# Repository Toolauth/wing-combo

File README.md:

# Combined Use Board
This is the **flagship board** for the [Toolauth](https://github.com/Toolauth) project.  More information about use, setup, and firmware is available in [this repo's wiki](https://github.com/Toolauth/wing-combo/wiki).

It can allow for the management of power tools, and serve as the gateway for user authorization in a shared workshop.

The board has the following features:
* A stack of relays & a contactor for controlling power to the downstream tool.
* Its own power supply, to draw from the line supplying the downstream tool (_no extra power needed, if under 220VAC_).
* An ADE7953 current sensor, to monitor energy use/ status of the connected tool.
* Connectors to add in an RFID card reader (_workshop member's badges can swipe_).
* Connections for a hardware bypass, for quick-enabling of the tool.
* Simple connection for panel-mounted Red & Green status LEDs.
* 5V supply (from onboard transformer) in USB and solder-able form, for future expansion.

## How do I play with this PCB design?
It is as easy as downloading this design by whatever means you like: zip file, `clone`, etc. Then, open the `wing-combo.kicad_pro` file with any version of [KiCAD](https://www.kicad.org/) you like, but the newest version will probably be best.

## Adafuit Feather Specification
In avoidance of obsolescence, we have designed this board to the [Adafruit](https://www.adafruit.com/)'s [Feather Specification](https://learn.adafruit.com/adafruit-feather/feather-specification). The logic here is that the Feather specification itself should allow us to upgrade the 'brain' of this wing without needing a major re-design. 

_Yes, we could have designed a specific ESP32 into the board. But experience with previous generations has taught us that it is more convenient to make the boards with a MAC address removable._

## IOT Hosting
This project was designed to work with [Home Assistant](https://www.home-assistant.io/) and [ESPHome](https://esphome.io/), because they allow us to host the whole solution on-premises. However, this board is not tied to that stack by any means. There are lots of ways firmware and software could come together to make this work.

## Design Software
* Schematic and board designed in [KiCAD](https://www.kicad.org/).
* Graphics designed in [Inkscape](https://inkscape.org/).
* Ordered as assembled boards from [JLCPCB](https://jlcpcb.com/).

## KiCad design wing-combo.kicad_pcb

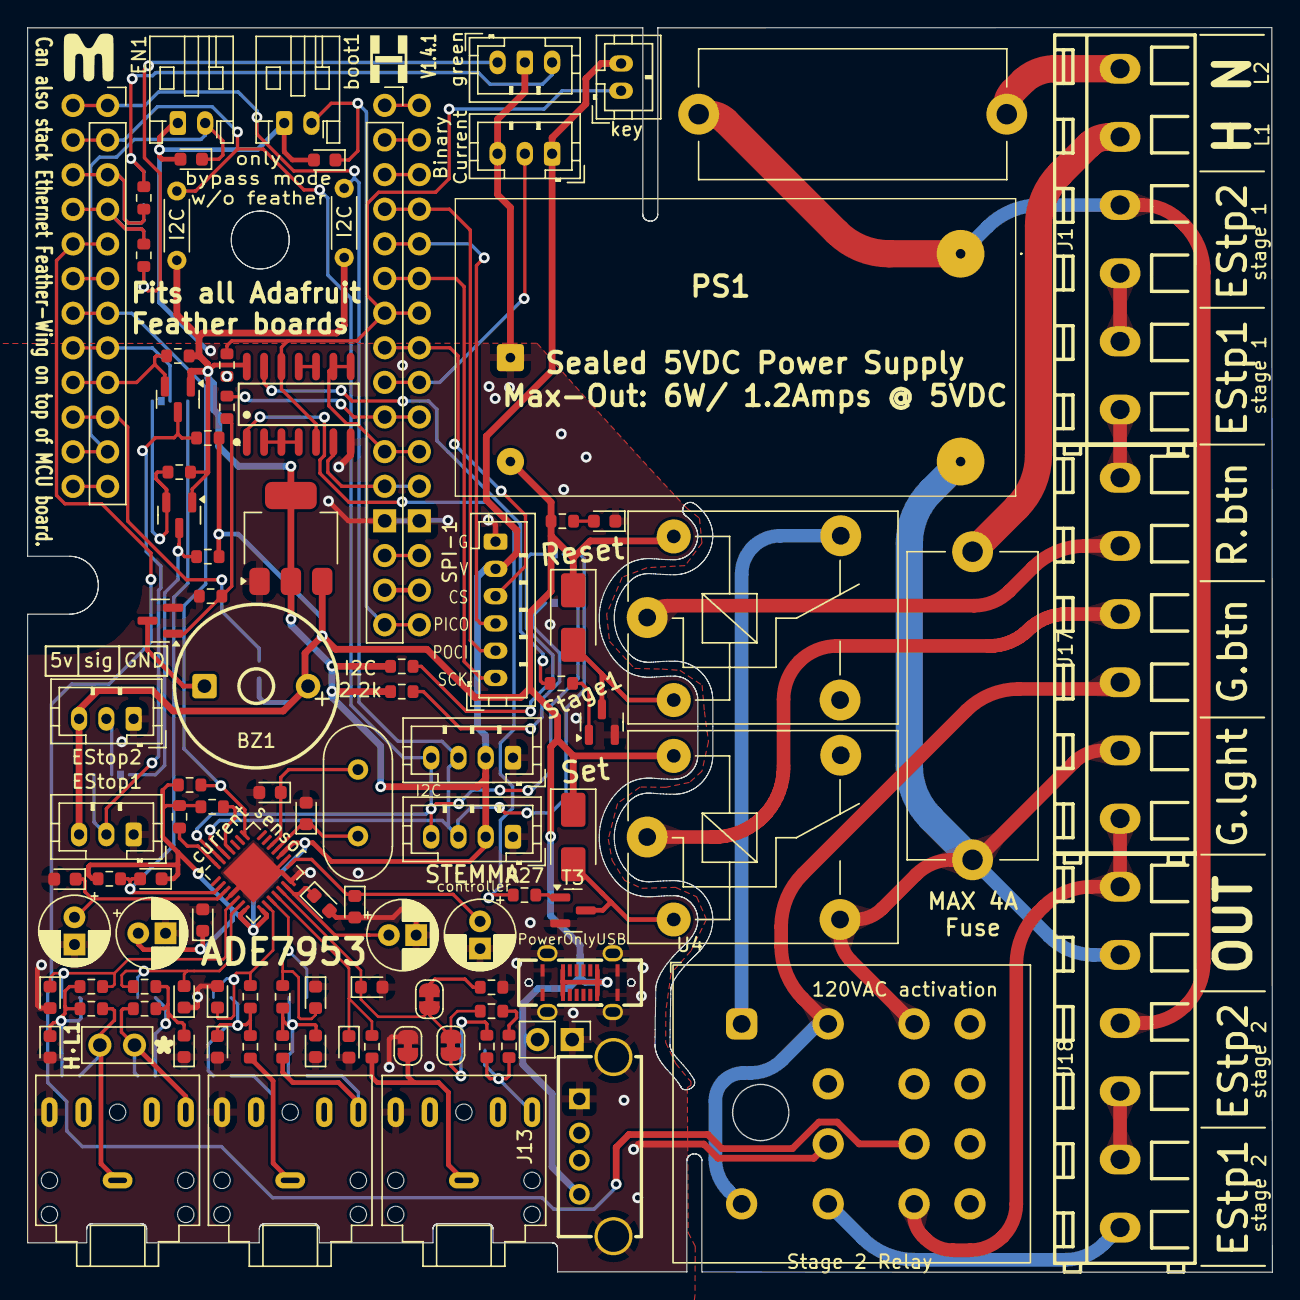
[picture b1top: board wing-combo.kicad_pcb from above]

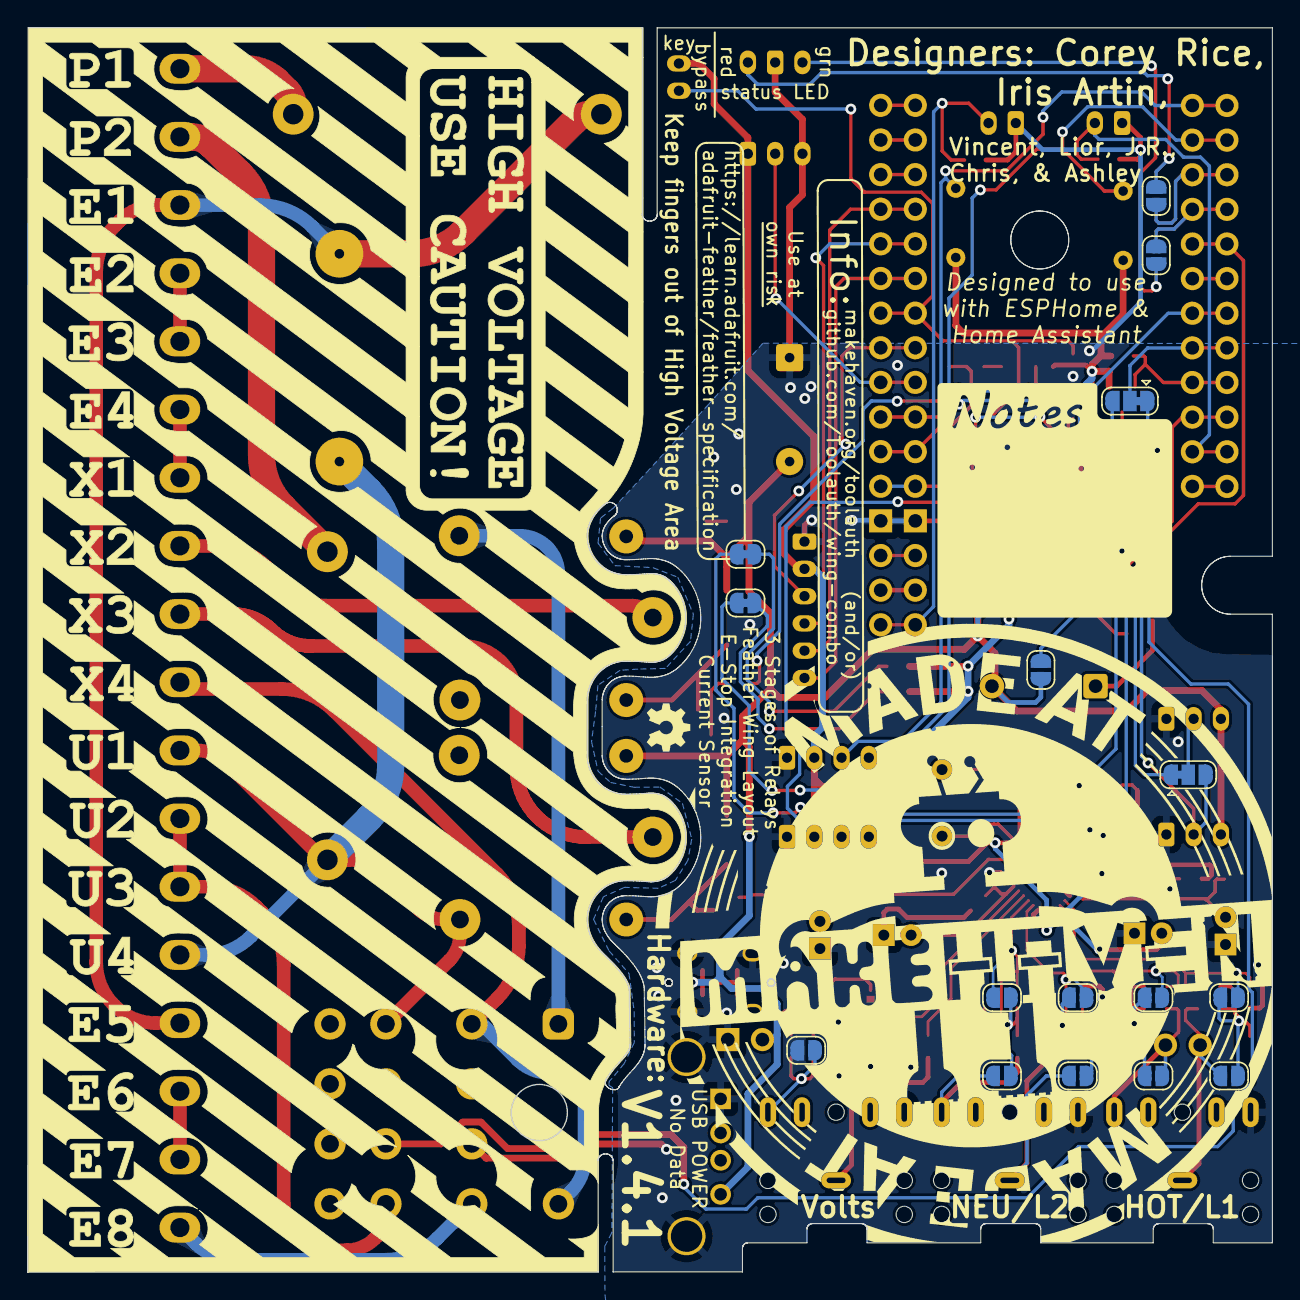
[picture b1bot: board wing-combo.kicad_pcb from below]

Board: 2 copper layers, 91.3 x 91.2 mm, 118 parts (16 on the bottom side), 89 nets.

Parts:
BZ1: Buzzer; BUZ-TH_BD12.0-P7.60-D0.6-FD
Bypass-1: Conn_01x02_Female; JST_PH_B2B-PH-K_1x02_P2.00mm_Vertical
C1, C2: 0.1uF; LED_0603_1608Metric
C3, C4, C5, C6, C7, C8, C9, C10, C11, C12: 33nF; LED_0603_1608Metric
C13, C16, C17, C22: 100nF; LED_0603_1608Metric
C14: 10uF; CP_Radial_D5.0mm_P2.00mm
C15: 1uF; LED_0603_1608Metric
C18, C19, C23: 4.7uF; CP_Radial_D5.0mm_P2.00mm
C20, C21: 20pF; LED_0603_1608Metric
D2: LED; LED_0603_1608Metric
D3, D4: SS14; D_SMA
EN1: Conn_01x02_Female; JST_PH_S2B-PH-K_1x02_P2.00mm_Horizontal
EStop1, EStop2: Conn_01x03_Female; JST_PH_B3B-PH-K_1x03_P2.00mm_Vertical
F1, F2: Fuse; Fuseholder_Cylinder-5x20mm_Stelvio-Kontek_PTF78_Horizontal_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
I2C-2: JST_PH_B4B-PH-K_1x04_P2.00mm_Vertical
I2C-3: Conn_01x04_Female; JST_PH_B4B-PH-K_1x04_P2.00mm_Vertical
IN-AUX-1: H/L1; PinHeader_1x02_P2.54mm_Vertical
J1, J17, J18: Screw_Terminal_01x06; CONN-TH_6P-P5.00_MX128-5.0-06P-GN01-CU-Y-A
J3, J4: Conn_01x12; PinSocket_1x12_P2.54mm_Vertical
J5: USB_C_Receptacle_USB2.0_16P; USB-C-TH_GT-USB-7055
J6: H/L1; Jack_3.5mm_CUI_SJ1-3525N_Horizontal
J7: N/L2; Jack_3.5mm_CUI_SJ1-3525N_Horizontal
J8: VOLTS; Jack_3.5mm_CUI_SJ1-3525N_Horizontal
J13: USB_A; USB-A-TH_USB-2.0-A-F-180-JCJ-H20.5
J15, J16: Conn_01x16; PinSocket_1x16_P2.54mm_Vertical
JP1, JP2, JP3, JP4, JP5, JP8, JP9, JP10, JP11, JP15, JP16, JP17: no-filter-1; SolderJumper-2_P1.3mm_Open_RoundedPad1.0x1.5mm
JP6, JP7, JP12, JP18, JP19: bridged; SolderJumper-2_P1.3mm_Bridged_RoundedPad1.0x1.5mm
JP13, JP14: SolderJumper_3_Bridged12; SolderJumper-3_P1.3mm_Bridged12_RoundedPad1.0x1.5mm
PS1: CFM06S050; CFM06S050E
R1, R5, R6, R14, R15, R16, R17, R18, R20, R21, R26, R27, R40: 1k; R_0603_1608Metric
R2, R3, R4, R22, R23, R24, R25, R28, R34, R35: 10k; R_0603_1608Metric
R7, R8: 2.2k; R_0603_1608Metric
R9, R10, R11, R12: 100; R_0603_1608Metric
R13, R19: 499k; R_0603_1608Metric
R32, R33: R_US; R_Axial_DIN0204_L3.6mm_D1.6mm_P5.08mm_Horizontal
R-G-LED1: Conn_01x03_Female; JST_PH_B3B-PH-K_1x03_P2.00mm_Vertical
SPI-1: Conn_01x06_Female; JST_PH_B6B-PH-K_1x06_P2.00mm_Vertical
T1, T2, T3, T4, T6: AO3400A; SOT-23
U1: 74HC02; SOIC-14_L8.7-W3.9-P1.27-LS6.0-BL
U2: ADE7953xCP; LFCSP-28-1EP_5x5mm_P0.5mm_EP3.14x3.14mm
U3: AMS1117-3.3; SOT-223-3_TabPin2
U4: PY14-02; Relay_Socket_4PDT_Omron_PY14-02-local
Y1: 3.58MHz; Crystal_HC49-4H_Vertical
binary-current1: Conn_01x03_Female; JST_PH_B3B-PH-K_1x03_P2.00mm_Vertical
boot1: Conn_01x02_Female; JST_PH_S2B-PH-K_1x02_P2.00mm_Horizontal
pwr5v1: extra; PinHeader_1x02_P2.54mm_Vertical
relay1, relay2: JQC-3FF/005-1ZS(551); Relay_SPDT_SANYOU_SRD_Series_Form_C

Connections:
+3.3V: Bypass-1.2, C13.1, C14.1, C15.1, I2C-2.2, I2C-3.2, R3.2, R7.2, R8.2, R22.2, R23.2, R24.2, R25.2, R32.1, R33.1, R34.2, SPI-1.5, T2.1 (G), T6.1 (G), U1.14 (VCC), U2.7 (PULL_HIGH), U2.8 (PULL_HIGH), U2.17 (VDD), U3.2 (VO), binary-current1.1
+3.3VA: J15.15, J16.15
+5V: BZ1.1 (+), D3.1 (K), D4.1 (K), EStop1.3, EStop2.3, J5.A4 (VBUS), J5.A9 (VBUS), J5.B4 (VBUS), J5.B9 (VBUS), J13.1 (VBUS), JP17.2 (B), PS1.3 (+VOUT), R4.2, R26.2, R35.2, U3.3 (VI), pwr5v1.2, relay1.5, relay2.5
/microcontroller/lightsounds/dcp1: BZ1.2 (-), T1.3 (D)
CS: R24.1, U2.28 (~CS)
CS-eth0: J3.6, J4.6
CS-jst: J15.8, J16.8, SPI-1.4
DC-read-stage2: J3.5, J4.5, U4.7 (sw3-no)
EN: C2.1, EN1.1, J3.11, J4.11
GND: C1.2, C2.2, C3.2, C4.1, C5.2, C6.1, C7.2, C8.1, C9.2, C10.1, C11.2, C12.2, C13.2, C14.2, C16.2, C17.2, C18.2, C19.2, C20.2, C21.2, C22.2, C23.2, D2.1 (K), EN1.2, EStop1.1, EStop2.1, I2C-2.1, I2C-3.1, J5.A1 (GND), J5.A12 (GND), J5.B1 (GND), J5.B12 (GND), J5.S1 (SHIELD), J6.R, J7.R, J8.R, J13.4 (GND), J13.5 (Shield), J13.6, J15.13, J16.13, JP1.1 (A), JP6.1 (A), PS1.4 (-VOUT), R2.1, R21.2, R28.1, R-G-LED1.2, SPI-1.6, T1.2 (S), T3.2 (S), T4.2 (S), U1.7 (GND), U2.4 (DGND), U2.14 (PULL_LOW), U2.16 (AGND), U2.29 (EP), U3.1 (GND), U4.11 (sw3-com), binary-current1.3, boot1.2, pwr5v1.1
Green-Indicator-light-1: F1.2, J17.2, J18.5, PS1.2 (ACL), U4.5 (sw1-no), relay1.3
Green-Indicator-light-2: J17.1, J18.6, U4.8 (sw4-no)
H/L1: F1.1, J1.5
IAN: C8.2, JP9.1 (A), R16.1, U2.6 (IAN)
IAN_IN: IN-AUX-1.2, J6.T, JP3.2 (B), R10.2
IAP: C7.1, JP8.2 (B), R15.2, U2.5 (IAP)
IAP_IN: IN-AUX-1.1, J6.S, JP2.1 (A), R9.1
IBN: C10.2, JP11.1 (A), R18.1, U2.10 (IBN)
IBN_IN: J7.T, JP5.2 (B), R12.2
IBP: C9.1, JP10.2 (B), R17.2, U2.9 (IBP)
IBP_IN: J7.S, JP4.1 (A), R11.1
Member-E-Stop-aux1-1: J18.2, J18.3
Member-E-Stop-aux2-1: J1.2, J1.3
Member-E-Stop-aux2-2: F2.2, J1.4, J18.4, PS1.1 (ACN)
Member-E-Stop-sw1-1: J18.1, U4.12 (sw4-com)
Member-E-Stop-sw2-1: J1.1, J17.6
Member-Green-Button-1: J17.4, relay1.1
Member-Green-Button-2: J17.3, U4.9 (sw1-com), U4.14 (solenoid)
Member-Red-Reset-Button-1: J17.5, relay2.1
unnamed: D2.2 (A), R26.1
unnamed: D3.2 (A), T3.3 (D), relay1.2
unnamed: D4.2 (A), T4.3 (D), relay2.2
unnamed: EStop1.2, JP14.3 (B), R4.1, T2.3 (D)
unnamed: EStop2.2, JP14.2 (C)
unnamed: J3.10, J4.10, JP17.1 (A)
unnamed: J3.12, J4.12
unnamed: J15.1, J16.1
unnamed: J15.2, J16.2
unnamed: J15.3, J16.3
unnamed: J15.14, J16.14
unnamed: C3.1, JP2.2 (B), JP8.1 (A), R9.2, R15.1
unnamed: C4.2, JP3.1 (A), JP9.2 (B), R10.1, R16.2
unnamed: JP7.1 (A), R14.1
unnamed: C5.1, JP4.2 (B), JP10.1 (A), R11.2, R17.1
unnamed: C6.2, JP5.1 (A), JP11.2 (B), R12.1, R18.2
unnamed: JP12.1 (A), R21.1
unnamed: C15.2, JP13.3 (B), R22.1, U2.2 (~RESET)
unnamed: JP14.1 (A), R35.1, T6.3 (D)
unnamed: JP15.2 (B), R5.2, R-G-LED1.3
unnamed: JP16.2 (B), R6.1, R-G-LED1.1
unnamed: JP18.2 (B), R8.1
unnamed: JP19.2 (B), R7.1
unnamed: R13.1, R19.2
unnamed: R27.1, U1.1
unnamed: R40.1, U1.13
unnamed: R1.2, R2.2, T1.1 (G)
unnamed: R27.2, T3.1 (G)
unnamed: R40.2, T4.1 (G)
unnamed: U1.2, U1.3, U1.4
unnamed: U1.10, U1.11
unnamed: C21.1, U2.18 (CLKIN), Y1.1
unnamed: C20.1, U2.19 (CLKOUT), Y1.2
unnamed: C22.1, C23.1, U2.13 (REF)
unnamed: C17.1, C19.1, U2.15 (VINTA)
unnamed: C16.1, C18.1, U2.3 (VINTD)
N/L2: F2.1, J1.6
PICO: J15.5, J16.5, SPI-1.3
POCI: J15.4, J16.4, SPI-1.2
SCK: J15.6, J16.6, SPI-1.1
SCL: I2C-2.4, I2C-3.4, J3.2, J4.2, JP18.1 (A), R33.2, U2.27 (MOSI/SCL/RX)
SCLK: R25.1, U2.25 (SCLK)
SDA: I2C-2.3, I2C-3.3, J3.1, J4.1, JP19.1 (A), R32.2, U2.26 (MISO/SDA/TX)
VN: C12.1, R20.1, U2.11 (VN)
VN_IN: J8.S, JP6.2 (B), R20.2
VP: C11.1, JP7.2 (B), JP12.2 (B), R19.1, U2.12 (VP)
VP_IN: J8.T, JP1.2 (B), R13.2, R14.2
ade7953-IRQ: J3.7, J4.7, R23.1, U2.22 (~IRQ)
binary-current: J15.9, J16.9, binary-current1.2
boot: C1.1, J15.16, J16.16, boot1.1
buzz: J15.10, J16.10, R1.1
led-grn: J3.4, J4.4, JP16.1 (A), R6.2
led-red: J3.3, J4.3, JP15.1 (A), R5.1
read-E-Stop: J3.9, J4.9, R3.1, T2.2 (S)
read-aux-E-Stop: JP13.1 (A), R34.1, T6.2 (S)
read-bypass: Bypass-1.1, J15.7, J16.7, R28.2, U1.5, U1.12
reset: U4.13 (solenoid), relay2.4
reset3v: J15.11, J16.11, U1.8, U1.9
set3v: J15.12, J16.12, U1.6
two-options: J3.8, J4.8, JP13.2 (C)

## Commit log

2024-03-07 remove reader ~ in a different project
2024-03-07 simplify the ESPHome test firmware
2024-03-07 dereference secret.yaml file
2024-03-07 move board into main repo
2024-03-07 remove website things
2024-03-07 remove reader-daughter images
2024-03-07 reorganize images
2024-03-07 reorganize
2024-03-07 simplify esphome firmwre test
2024-03-07 remove reader-daughter (has its own repo now)
2024-03-07 missed two
2024-03-07 remove website
2024-03-07 remove reader daughter
2024-03-07 geometry naming convention
2024-03-07 new folder readme
2024-03-07 how do I play?
2024-03-07 formatting touchup
2024-03-07 typo
2024-03-10 update docs images
2024-03-10 move readme
2024-03-10 fix typos
2024-03-10 hero images
2024-03-10 fix relative link
2024-03-10 do not default to main
2024-03-29 rename esphome hello-world
2024-03-29 start Arduino hello-world
2024-05-24 restructure hello-world-firmware
2024-05-24 add empty firmware folders
2024-05-24 added basic Arduino io_test
2024-05-26 hero-img
2024-05-26 image fixes
2024-05-26 add location-feather-seat
2024-05-31 double-check mains connections, update notes
2024-05-31 fix missed-items from merge conflict resolution
2024-05-31 F.Cu visible
2024-08-02 change URL on board to makehaven.org/toolauth, to match with Project name on GitHub
2024-08-02 unpopulate headers that are not needed
2024-11-17 added candidate changes to accomodate Adafruit Ethernet feather-wing
2024-11-28 add j151 relay documentation
2024-11-28 first draft footprint
2024-11-29 fixed j151 relay footprint...probably. also ordered physical relays to confirm
2024-11-29 connected footprint to 3D model
2024-12-03 convert to new parts on the board: footprint change for relay and wishlist-JST connectors
2024-12-06 update gitignore
2024-12-06 added screw terminls from LCSC library
2024-12-06 placed new screw terminals on board
2024-12-06 flipped arbitrary pin-numberrs on relay, for better routing
2024-12-06 save lcsc part number
2024-12-10 candidate reconfiguration for bypass key operation and sensing
2024-12-10 reassigned netclasses, removed vestigial level-shifter
2024-12-10 flip pins on bypass key for better wire-routing
2024-12-10 [fix] bypass key and high-voltage routing
2024-12-10 [fix] read-bypass link
2024-12-10 [new] assigned CS pin for JST-SPI and Ethernet Feather-Wing
2024-12-10 update gitignore to exclude venv for kicad scripts
2024-12-10 added more parts from EasyEDA with the easyeda2kicad script
2024-12-10 added 3D models to design
2024-12-11 [fix] PICO/POCI flipped on Feather Boards
2024-12-11 added USBC, much to Vincent's delight :)
2024-12-11 added USBC for power. Changed Feather power-supply to be incompliance with Feather's recommendations
2024-12-11 added lcsc_id
2024-12-12 fun new shapes!
2024-12-12 fix USBC-vertical footprint drill holes
2024-12-12 bugfixes galore!
2024-12-12 missed this one on a previous commit
2024-12-13 add ADE7953 to the odd-parts folder (mostly for a 3D footprint)
2024-12-13 add 3D model of ADE7953
2024-12-24 improved F.silkscreen for before hand-soldering
2025-01-06 moved LED GPIO to fit free pins for ethernet wing
2025-01-22 working through DRC checks
2025-01-23 usbc schematic/footprint aligned
2025-02-05 ordered B1P3 test run from JLCPCB
2025-02-05 added interactive BOM
2025-02-05 update images
2025-02-17 bypass key disables reset relay. Based on recommendation from Lior
2025-02-25 added 74HC02 to stage 1 relay schematic
2025-02-25 update text
2025-02-26 made a note of JLC2KiCad_lib
2025-07-04 parts for bypass XOR
2025-07-04 cleanup
2025-07-04 rename misspelled file
2025-07-04 changed to py14-02 relay socket
2025-07-04 local variant of PY14-02 footprint
2025-07-04 [auto] annotate schematic
2025-09-21 1.4.1 schematic update
2025-09-21 py14-02 socket
2025-09-21 3d model for relay socket
2025-09-21 partway progress
2025-09-21 exported shapes for silkscreen design
2025-09-21 handled DRC errors on board design
2025-09-22 update jumper numbers
2025-09-22 update jumper numbers pt2
2025-09-22 clean geometry folder
2025-09-22 cartoon drawing of how to wire E-Stop
2025-09-22 PCB update
2025-09-22 remove unused parts
2025-09-22 relocate PY14 socker step file
2025-09-22 baord versioning on silkscreen
2025-09-22 added more layers and labels
2025-09-22 refined layers and labels
2025-09-23 update traces on USB-A
2025-09-24 near-final layout
2025-09-24 near-final silkscreen
2025-09-24 silkscreen on PCB
2025-09-26 update interactive bom
2025-09-26 update reference values for better ibom
2025-09-26 migrate better reference values to board
2025-10-05 before new branch
2025-10-08 added secondary git ignore
2025-10-09 nearly ready
2025-10-15 new board shapes
2025-10-15 5v binary current and cleanup
2025-10-25 close enough for 3D export
2025-10-25 add project page with redirects
2025-10-25 better user interface
2025-10-31 about to order v1.4.3
2025-11-02 commit production files
2025-11-03 add action for releases
2025-11-03 merged shift-bin-cur
2025-11-03 rename and cleanup
2025-11-03 remove legacy odd-parts
2025-11-03 moved to kicad 9
2025-11-03 added power-jumper location
2025-11-03 touchup schematic pdf
2025-11-03 improved responsiveness
2025-11-04 update gitignore setup
2025-11-04 remove previous version
2025-11-04 remove netlist
2025-11-04 added two options
2025-11-04 ignore netlist.ipc
2025-11-04 nearly ready for v1.4.4
2025-11-04 added fiducials
2025-11-09 new v1.4.4 hello-world firmware
2025-11-09 ignore sierra-circuit logs
2026-02-16 updated to match v1.4 boards
2026-04-01 tested IRL
2026-04-06 been a minute: preserve changes
2026-04-07 first pass
2026-04-08 change to standard fn comment style...
2026-04-08 nonblocking focus
2026-04-08 observe with struct
2026-04-08 getting ready for compilation
2026-04-08 firmware compiles
2026-04-08 remove notes
2026-04-10 debounce, timedelta, sw_restart
2026-04-10 watchdog + software restart
2026-04-10 default time until board does a software reset
2026-04-10 watchdog, debounce, OTA updates
2026-04-10 added ESP32Ping
2026-04-10 added README
2026-04-11 add config for Home Assistant's default MQTT broker
2026-04-11 ha-compliance test 1
2026-04-11 better MQTT discovery
